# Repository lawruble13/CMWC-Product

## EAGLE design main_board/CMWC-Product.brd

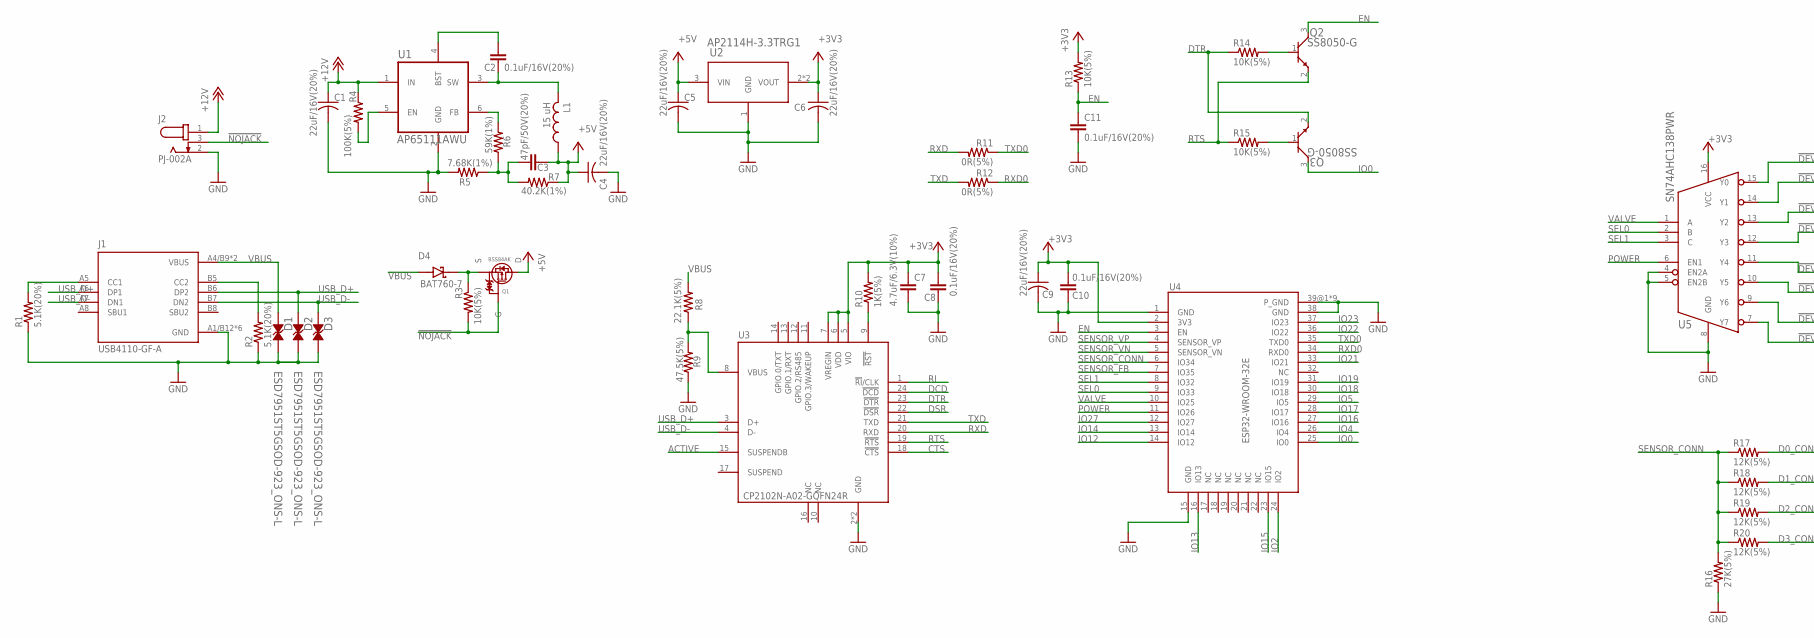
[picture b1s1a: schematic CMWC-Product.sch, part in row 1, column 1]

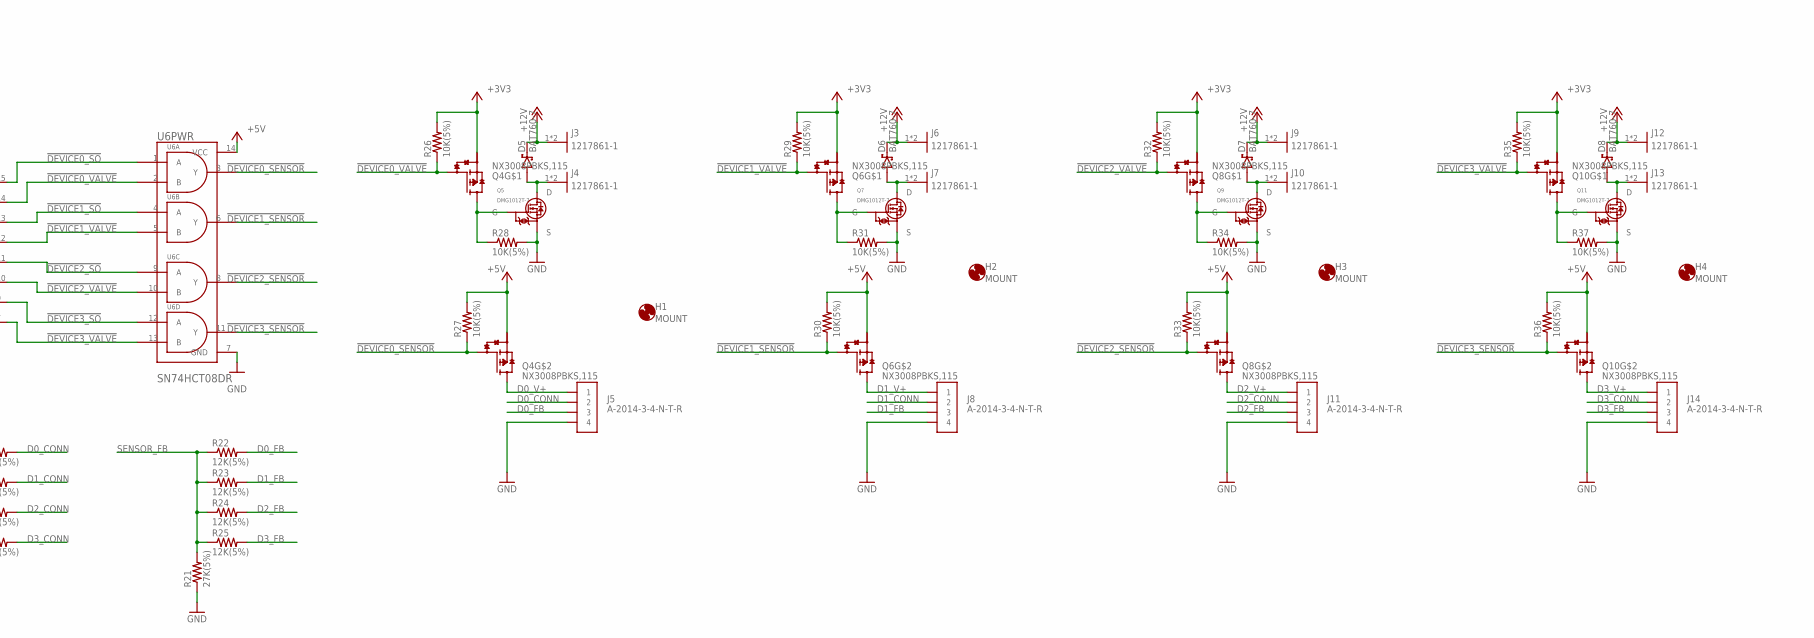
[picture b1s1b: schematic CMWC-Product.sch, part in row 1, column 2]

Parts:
C1, C4, C5, C6, C9: 22uF/16V(20%); C1206; DIGI-KEY_PART_NUMBER 1276-2728-1-ND
C2, C8, C10, C11: 0.1uF/16V(20%); C0603; DIGI-KEY_PART_NUMBER 399-1099-1-ND
C3: 47pF/50V(20%); C0603; DIGI-KEY_PART_NUMBER 399-1099-1-ND
C7: 4.7uF/6.3V(10%); C0603; DIGI-KEY_PART_NUMBER 1276-1045-1-ND
D1, D2, D3: ESD7951ST5GSOD-923_ONS-L; SOD-923_ONS-L
D4, D5, D6, D7, D8: BAT760-7; SOD2513X120N
H1, H2, H3, H4: MOUNT; #6-MOUNT
J1: USB4110-GF-A; GCT_USB4110-GF-A
J2: PJ-002A; CUI_PJ-002A
J3, J4, J6, J7, J9, J10, J12, J13: 1217861-1; TE_1217861-1
J5, J8, J11, J14: A-2014-3-4-N-T-R
L1: 15 uH; BWVS00505040
Q1: BSS84AK; TO236
Q2, Q3: SS8050-G; TRAN_SS8050-G_CIP
Q4, Q6, Q8, Q10: NX3008PBKS,115; SOT65P210X110-6N
Q5, Q7, Q9, Q11: DMG1012T-7; SOT523
R1, R2: 5.1K(20%); R0603; DIGI-KEY_PART_NUMBER RR08P5.1KDCT-ND
R3, R13, R14, R15, R26, R27, R28, R29, R30, R31, R32, R33, R34, R35, R36, R37: 10K(5%); R0603; DIGI-KEY_PART_NUMBER RNCP0603FTD10K0CT-ND
R4: 100K(5%); R0603; DIGI-KEY_PART_NUMBER RR08P100KDCT-ND
R5: 7.68K(1%); R0603; DIGI-KEY_PART_NUMBER 541-768HCT-ND
R6: 59K(1%); R0603; DIGI-KEY_PART_NUMBER RMCF0603FT59K0CT-ND
R7: 40.2K(1%); R0603; DIGI-KEY_PART_NUMBER CR0603-FX-4022ELFCT-ND
R8: 22.1K(5%); R0603; DIGI-KEY_PART_NUMBER RR08P22.1KDCT-ND
R9: 47.5K(5%); R0603; DIGI-KEY_PART_NUMBER RR08P47.5KDCT-ND
R10: 1K(5%); R0603; DIGI-KEY_PART_NUMBER RR08P1.0KDCT-ND
R11, R12: 0R(5%); R0603; DIGI-KEY_PART_NUMBER CR0603-J/-000ELFCT-ND
R16, R21: 27K(5%); R0603; DIGI-KEY_PART_NUMBER 541-27.0KHCT-ND
R17, R18, R19, R20, R22, R23, R24, R25: 12K(5%); R0603; DIGI-KEY_PART_NUMBER 311-2415-1-ND
U1: AP65111AWU; SOT95P280X100-6N
U2: AP2114H-3.3TRG1; SOT-223_DIO
U3: CP2102N-A02-GQFN24R; QFN50P400X400X80-25N
U4: ESP32-WROOM-32E
U5: SN74AHC138PWR; SOP65P640X120-16N
U6: SN74HCT08DR; SOIC127P600X175-14N

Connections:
!DEVICE0_SENSOR: Q4.5 (G2), R27.1, U6.3 (Y)
!DEVICE0_SO: U5.15 (Y0), U6.1 (A)
!DEVICE0_VALVE: Q4.2 (G1), R26.1, U5.14 (Y1), U6.2 (B)
!DEVICE1_SENSOR: Q6.5 (G2), R30.1, U6.6 (Y)
!DEVICE1_SO: U5.13 (Y2), U6.4 (A)
!DEVICE1_VALVE: Q6.2 (G1), R29.1, U5.12 (Y3), U6.5 (B)
!DEVICE2_SENSOR: Q8.5 (G2), R33.1, U6.8 (Y)
!DEVICE2_SO: U5.11 (Y4), U6.9 (A)
!DEVICE2_VALVE: Q8.2 (G1), R32.1, U5.10 (Y5), U6.10 (B)
!DEVICE3_SENSOR: Q10.5 (G2), R36.1, U6.11 (Y)
!DEVICE3_SO: U5.9 (Y6), U6.12 (A)
!DEVICE3_VALVE: Q10.2 (G1), R35.1, U5.7 (Y7), U6.13 (B)
!NOJACK: J2.3, Q1.G, R3.2
+3V3: C6.1, C7.1, C8.1, C9.1, C10.1, Q4.1 (S1), Q6.1 (S1), Q8.1 (S1), Q10.1 (S1), R10.2, R13.2, R26.2, R29.2, R32.2, R35.2, U2.2 (VOUT), U2.4 (VOUT), U3.5 (VIO), U3.6 (VDD), U3.7 (VREGIN), U4.2 (3V3), U5.16 (VCC)
+5V: C3.2, C4.1, C5.1, L1.P$1 (1), Q1.D, Q4.4 (S2), Q6.4 (S2), Q8.4 (S2), Q10.4 (S2), R7.1, R27.2, R30.2, R33.2, R36.2, U2.3 (VIN), U6.14 (VCC)
+12V: C1.1, D5.C, D6.C, D7.C, D8.C, J2.1, J3.1, J3.2, J6.1, J6.2, J9.1, J9.2, J12.1, J12.2, R4.1, U1.1 (IN)
ACTIVE: U3.15 (SUSPENDB)
BUCK_BST: C2.1, U1.4 (BST)
BUCK_EN: R4.2, U1.5 (EN)
BUCK_FB: R6.2, U1.6 (FB)
BUCK_SW: C2.2, L1.P$2 (2), U1.3 (SW)
CTS: U3.18 (!CTS)
D0_CONN: J5.2, R17.2
D0_FB: J5.3, R22.2
D0_V+: J5.1, Q4.3 (D2)
D1_CONN: J8.2, R18.2
D1_FB: J8.3, R23.2
D1_V+: J8.1, Q6.3 (D2)
D2_CONN: J11.2, R19.2
D2_FB: J11.3, R24.2
D2_V+: J11.1, Q8.3 (D2)
D3_CONN: J14.2, R20.2
D3_FB: J14.3, R25.2
D3_V+: J14.1, Q10.3 (D2)
DCD: U3.24 (!DCD)
DSR: U3.22 (!DSR)
DTR: Q3.2, R14.1, U3.23 (!DTR)
EN: C11.1, Q2.3, R13.1, U4.3 (EN)
GND: C1.2, C4.2, C5.2, C6.2, C7.2, C8.2, C9.2, C10.2, C11.2, D1.1 (CATHODE), D2.1 (CATHODE), D3.1 (CATHODE), J1.A1/B12 (GND), J1.B1/A12 (GND), J1.S1 (GND), J1.S2 (GND), J1.S3 (GND), J1.S4 (GND), J2.2, J5.4, J8.4, J11.4, J14.4, Q5.1 (S), Q7.1 (S), Q9.1 (S), Q11.1 (S), R1.1, R2.1, R5.2, R9.1, R16.1, R21.1, R28.2, R31.2, R34.2, R37.2, U1.2 (GND), U2.1 (GND), U3.2 (GND), U3.25 (GND), U4.1 (GND), U4.15 (GND), U4.38 (GND), U4.39@1 (P_GND), U4.39@2 (P_GND), U4.39@3 (P_GND), U4.39@4 (P_GND), U4.39@5 (P_GND), U4.39@6 (P_GND), U4.39@7 (P_GND), U4.39@8 (P_GND), U4.39@9 (P_GND), U5.4 (EN2A), U5.5 (EN2B), U5.8 (GND), U6.7 (GND)
IO0: Q3.3, U4.25 (IO0)
IO2: U4.24 (IO2)
IO4: U4.26 (IO4)
IO5: U4.29 (IO5)
IO12: U4.14 (IO12)
IO13: U4.16 (IO13)
IO14: U4.13 (IO14)
IO15: U4.23 (IO15)
IO16: U4.27 (IO16)
IO17: U4.28 (IO17)
IO18: U4.30 (IO18)
IO19: U4.31 (IO19)
IO21: U4.33 (IO21)
IO22: U4.36 (IO22)
IO23: U4.37 (IO23)
IO27: U4.12 (IO27)
unnamed: D4.C, Q1.S, R3.1
unnamed: C3.1, R5.1, R6.1, R7.2
unnamed: J1.A5 (CC1), R1.2
unnamed: J1.B5 (CC2), R2.2
unnamed: R8.1, R9.2, U3.8 (VBUS)
unnamed: D5.A, J4.1, J4.2, Q5.3 (D)
unnamed: Q2.1, R14.2
unnamed: Q3.1, R15.2
unnamed: R10.1, U3.9 (!RST)
unnamed: Q4.6 (D1), Q5.2 (G), R28.1
unnamed: D6.A, J7.1, J7.2, Q7.3 (D)
unnamed: Q6.6 (D1), Q7.2 (G), R31.1
unnamed: D7.A, J10.1, J10.2, Q9.3 (D)
unnamed: Q8.6 (D1), Q9.2 (G), R34.1
unnamed: D8.A, J13.1, J13.2, Q11.3 (D)
unnamed: Q10.6 (D1), Q11.2 (G), R37.1
POWER: U4.11 (IO26), U5.6 (EN1)
RI: U3.1 (!RI!/CLK)
RTS: Q2.2, R15.1, U3.19 (!RTS)
RXD: R11.2, U3.20 (RXD)
RXD0: R12.1, U4.34 (RXD0)
SEL0: U4.9 (IO33), U5.2 (B)
SEL1: U4.8 (IO32), U5.3 (C)
SENSOR_CONN: R16.2, R17.1, R18.1, R19.1, R20.1, U4.6 (IO34)
SENSOR_FB: R21.2, R22.1, R23.1, R24.1, R25.1, U4.7 (IO35)
SENSOR_VN: U4.5 (SENSOR_VN)
SENSOR_VP: U4.4 (SENSOR_VP)
TXD: R12.2, U3.21 (TXD)
TXD0: R11.1, U4.35 (TXD0)
USB_D+: D2.2 (ANODE), J1.A6 (DP1), J1.B6 (DP2), U3.3 (D+)
USB_D-: D3.2 (ANODE), J1.A7 (DN1), J1.B7 (DN2), U3.4 (D-)
VALVE: U4.10 (IO25), U5.1 (A)
VBUS: D1.2 (ANODE), D4.A, J1.A4/B9 (VBUS), J1.B4/A9 (VBUS), R8.2

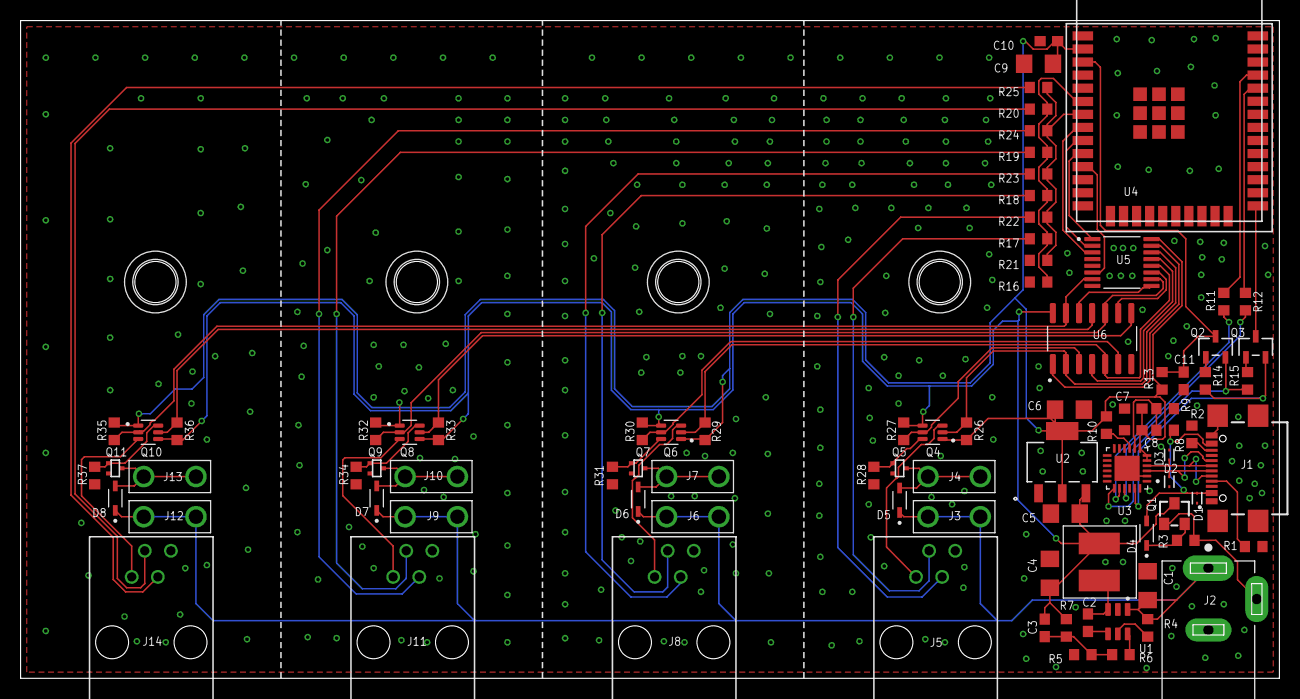
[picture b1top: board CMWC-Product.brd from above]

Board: 2 copper layers, 122.3 x 63.9 mm, 92 parts (0 on the bottom side), 66 nets.

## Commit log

2020-12-07 add README

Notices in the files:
parts and their libraries:
COPYRIGHT: Copyright (C) 2018 Accelerated Designs. All rights reserved
